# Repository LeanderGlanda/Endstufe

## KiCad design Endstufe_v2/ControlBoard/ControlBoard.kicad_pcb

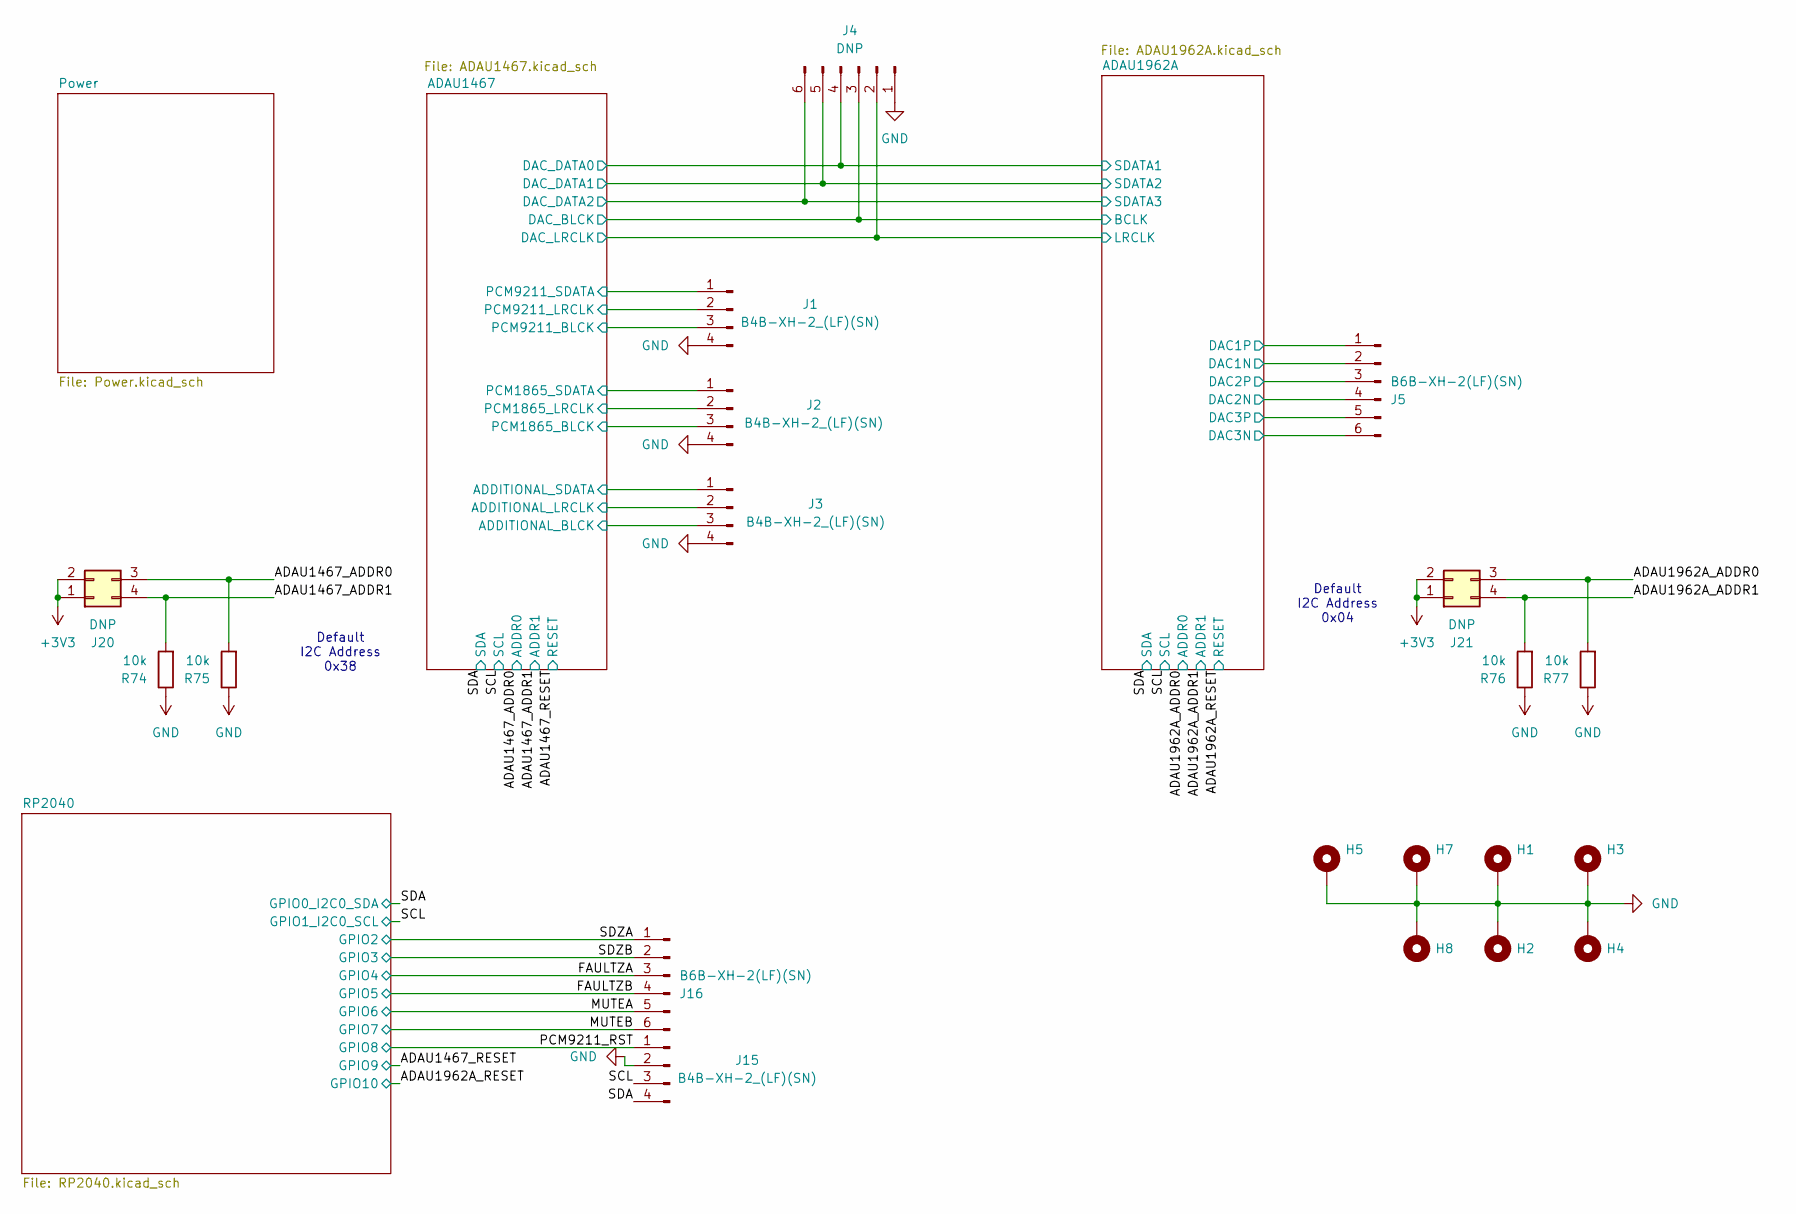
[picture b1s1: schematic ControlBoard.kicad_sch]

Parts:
H1, H2, H3, H4, H5, H7, H8: MountingHole_Pad; MountingHole_3.2mm_M3_ISO14580_Pad
J1, J2, J3, J15: B4B-XH-2_(LF)(SN); JST_XH_B4B-XH-A_1x04_P2.50mm_Vertical; LCSC C157999
J4: DNP; PinHeader_1x06_P2.54mm_Vertical
J5, J16: B6B-XH-2(LF)(SN); JST_XH_B6B-XH-A_1x06_P2.50mm_Vertical; LCSC C157986
J20, J21: DNP; PinHeader_2x02_P2.54mm_Vertical
R74, R75, R76, R77: 10k; C_0402_1005Metric; LCSC Part # C25744

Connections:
+3V3: J20.1, J20.2, J21.1, J21.2; also elsewhere on the board
/ADAU1467/ADDITIONAL_BLCK: J3.3; also elsewhere on the board
/ADAU1467/ADDITIONAL_LRCLK: J3.2; also elsewhere on the board
/ADAU1467/ADDITIONAL_SDATA: J3.1; also elsewhere on the board
/ADAU1467/DAC_BLCK: J4.3; also elsewhere on the board
/ADAU1467/DAC_DATA0: J4.4; also elsewhere on the board
/ADAU1467/DAC_DATA1: J4.5; also elsewhere on the board
/ADAU1467/DAC_DATA2: J4.6; also elsewhere on the board
/ADAU1467/DAC_LRCLK: J4.2; also elsewhere on the board
/ADAU1467/PCM1865_BLCK: J2.3; also elsewhere on the board
/ADAU1467/PCM1865_LRCLK: J2.2; also elsewhere on the board
/ADAU1467/PCM1865_SDATA: J2.1; also elsewhere on the board
/ADAU1467/PCM9211_BLCK: J1.3; also elsewhere on the board
/ADAU1467/PCM9211_LRCLK: J1.2; also elsewhere on the board
/ADAU1467/PCM9211_SDATA: J1.1; also elsewhere on the board
/ADAU1467_ADDR0: J20.3, R75.2; also elsewhere on the board
/ADAU1467_ADDR1: J20.4, R74.2; also elsewhere on the board
/ADAU1962A/DAC1N: J5.2; also elsewhere on the board
/ADAU1962A/DAC1P: J5.1; also elsewhere on the board
/ADAU1962A/DAC2N: J5.4; also elsewhere on the board
/ADAU1962A/DAC2P: J5.3; also elsewhere on the board
/ADAU1962A/DAC3N: J5.6; also elsewhere on the board
/ADAU1962A/DAC3P: J5.5; also elsewhere on the board
/ADAU1962A_ADDR0: J21.3, R77.2; also elsewhere on the board
/ADAU1962A_ADDR1: J21.4, R76.2; also elsewhere on the board
/FAULTZA: J16.3; also elsewhere on the board
/FAULTZB: J16.4; also elsewhere on the board
/MUTEA: J16.5; also elsewhere on the board
/MUTEB: J16.6; also elsewhere on the board
/PCM9211_RST: J15.1; also elsewhere on the board
/SCL: J15.3; also elsewhere on the board
/SDA: J15.4; also elsewhere on the board
/SDZA: J16.1; also elsewhere on the board
/SDZB: J16.2; also elsewhere on the board
GND: H1.1, H2.1, H3.1, H4.1, H5.1, H7.1, H8.1, J1.4, J2.4, J3.4, J4.1, J15.2, R74.1, R75.1, R76.1, R77.1; also elsewhere on the board

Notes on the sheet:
Default I2C Address 0x38
Default I2C Address 0x04

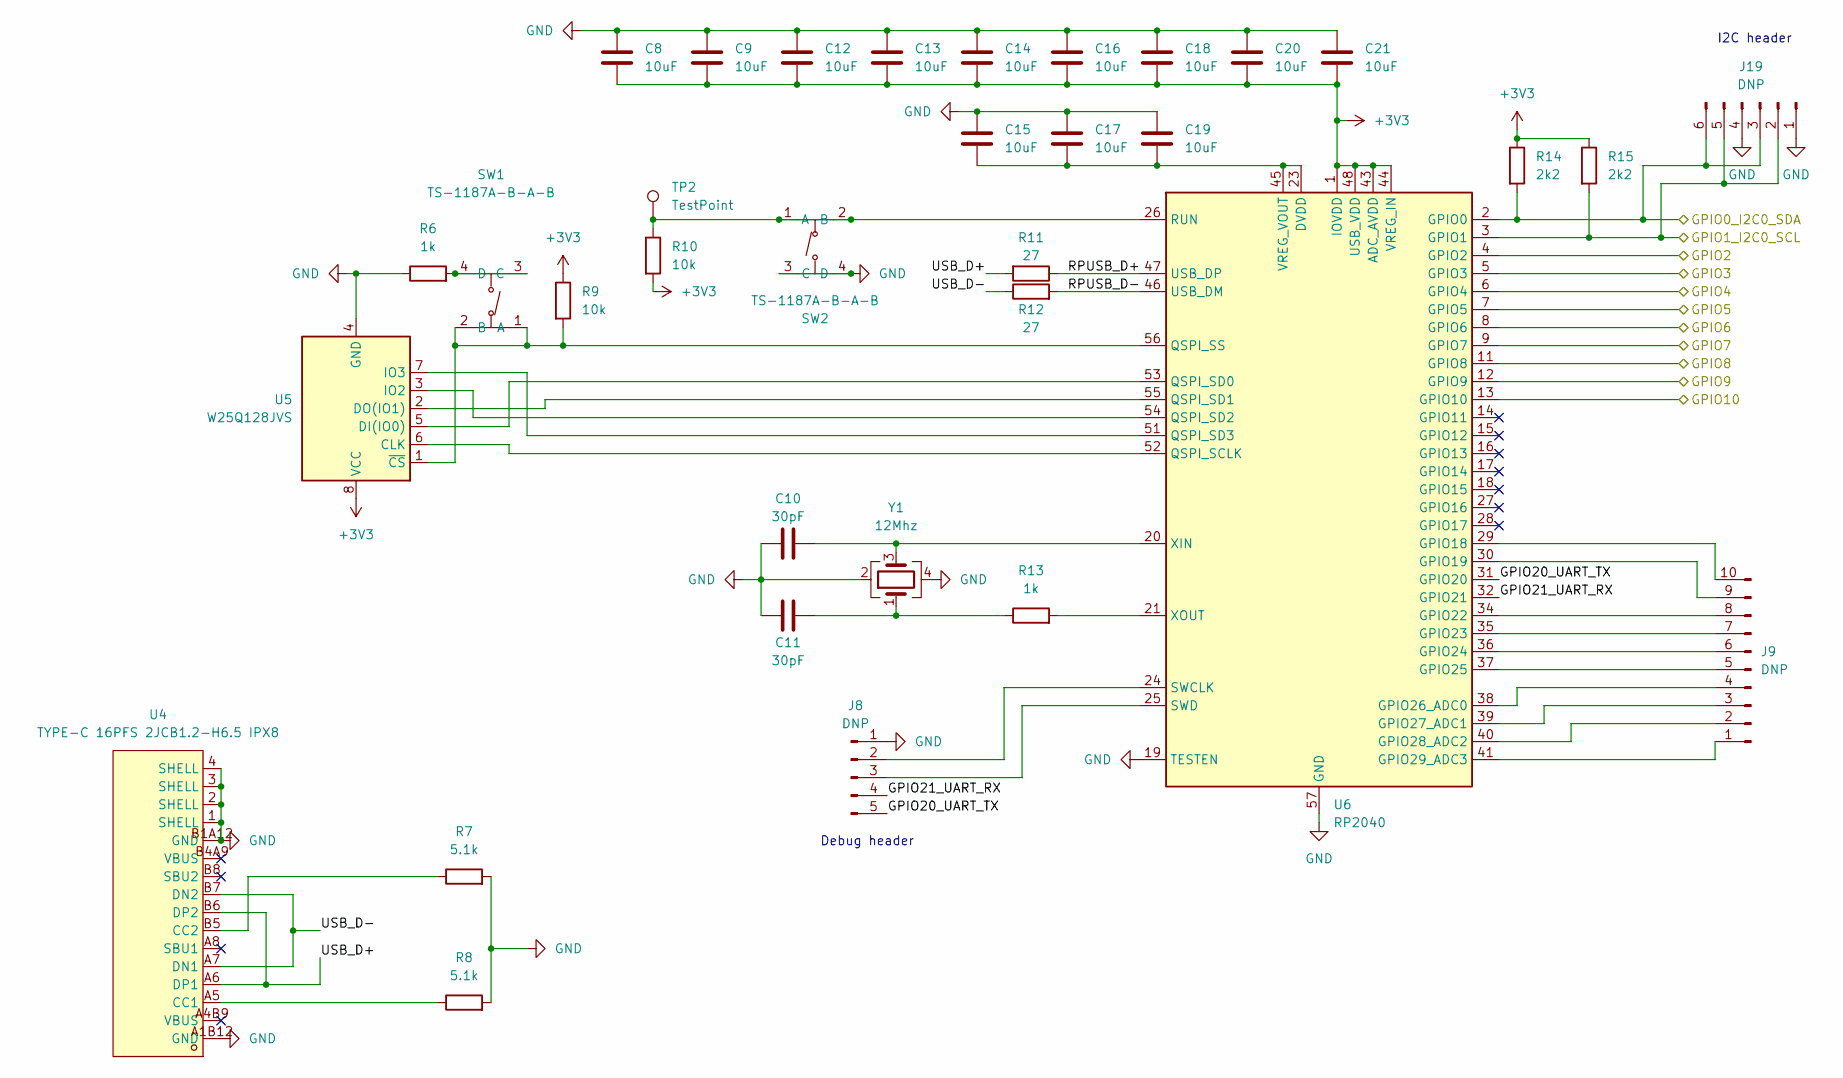
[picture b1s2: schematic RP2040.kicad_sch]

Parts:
C8, C9, C12, C13, C14, C15, C16, C17, C18, C19, C20, C21: 10uF; C_0402_1005Metric; LCSC Part # C15525
C10, C11: 30pF; C_0402_1005Metric; LCSC Part # C526980
J8: DNP; PinHeader_1x05_P2.54mm_Vertical
J9: DNP; PinHeader_1x10_P2.54mm_Vertical
J19: DNP; PinHeader_1x06_P2.54mm_Vertical
R6, R13: 1k; C_0402_1005Metric; LCSC Part # C11702
R7, R8: 5.1k; C_0603_1608Metric; LCSC Part # C2989458
R9, R10: 10k; C_0402_1005Metric; LCSC Part # C25744
R11, R12: 27; C_0603_1608Metric; LCSC Part # C2828673
R14, R15: 2k2; R_0805_2012Metric_Pad1.20x1.40mm_HandSolder; LCSC C17520
SW1, SW2: TS-1187A-B-A-B; SW-SMD_4P-L5.1-W5.1-P3.70-LS6.5-TL-2; LCSC Part # C318884
TP2: TestPoint; TestPoint_Pad_D1.0mm
U4: TYPE-C 16PFS 2JCB1.2-H6.5 IPX8; USB-C-SMD_TYPE-C16PIN; LCSC Part C393939
U5: W25Q128JVS; SOIC-8_L5.3-W5.3-P1.27-LS8.0-BL; LCSC Part # C97521
U6: RP2040; LQFN-56_L7.0-W7.0-P0.4-EP; LCSC Part # C2040
Y1: 12Mhz; OSC-SMD_4P-L3.2-W2.5-BL; LCSC Part # C9002

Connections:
+3V3: C8.2, C9.2, C12.2, C13.2, C14.2, C16.2, C18.2, C20.2, C21.2, R9.1, R10.2, R14.1, R15.1, U5.8 (VCC), U6.1 (IOVDD), U6.10 (IOVDD), U6.22 (IOVDD), U6.33 (IOVDD), U6.42 (IOVDD), U6.43 (ADC_AVDD), U6.44 (VREG_IN), U6.48 (USB_VDD), U6.49 (IOVDD); also elsewhere on the board
/ADAU1467_RESET: U6.12 (GPIO9); also elsewhere on the board
/ADAU1962A_RESET: U6.13 (GPIO10); also elsewhere on the board
/FAULTZA: U6.6 (GPIO4); also elsewhere on the board
/FAULTZB: U6.7 (GPIO5); also elsewhere on the board
/MUTEA: U6.8 (GPIO6); also elsewhere on the board
/MUTEB: U6.9 (GPIO7); also elsewhere on the board
/PCM9211_RST: U6.11 (GPIO8); also elsewhere on the board
/RP2040/GPIO20_UART_TX: J8.5, U6.31 (GPIO20)
/RP2040/GPIO21_UART_RX: J8.4, U6.32 (GPIO21)
/RP2040/RPUSB_D+: R11.1, U6.47 (USB_DP)
/RP2040/RPUSB_D-: R12.2, U6.46 (USB_DM)
/RP2040/USB_D+: R11.2, U4.A6 (DP1), U4.B6 (DP2)
/RP2040/USB_D-: R12.1, U4.A7 (DN1), U4.B7 (DN2)
/SCL: J19.2, J19.5, R15.2, U6.3 (GPIO1); also elsewhere on the board
/SDA: J19.3, J19.6, R14.2, U6.2 (GPIO0); also elsewhere on the board
/SDZA: U6.4 (GPIO2); also elsewhere on the board
/SDZB: U6.5 (GPIO3); also elsewhere on the board
GND: C8.1, C9.1, C10.1, C11.1, C12.1, C13.1, C14.1, C15.1, C16.1, C17.1, C18.1, C19.1, C20.1, C21.1, J8.1, J19.1, J19.4, R6.1, R7.2, R8.2, SW2.3 (C), SW2.4 (D), U4.1 (SHELL), U4.2 (SHELL), U4.3 (SHELL), U4.4 (SHELL), U4.A1B12 (GND), U4.B1A12 (GND), U5.4 (GND), U6.19 (TESTEN), U6.57 (GND), Y1.2, Y1.4; also elsewhere on the board
unnamed: C11.2, R13.1, Y1.1
unnamed: J8.2, U6.24 (SWCLK)
unnamed: J8.3, U6.25 (SWD)
unnamed: J9.1, U6.41 (GPIO29_ADC3)
unnamed: J9.2, U6.40 (GPIO28_ADC2)
unnamed: J9.3, U6.39 (GPIO27_ADC1)
unnamed: J9.4, U6.38 (GPIO26_ADC0)
unnamed: J9.5, U6.37 (GPIO25)
unnamed: J9.6, U6.36 (GPIO24)
unnamed: J9.7, U6.35 (GPIO23)
unnamed: J9.8, U6.34 (GPIO22)
unnamed: J9.9, U6.30 (GPIO19)
unnamed: J9.10, U6.29 (GPIO18)
unnamed: R9.2, SW1.1 (A), SW1.2 (B), U5.1 (~CS), U6.56 (QSPI_SS)
unnamed: R6.2, SW1.3 (C), SW1.4 (D)
unnamed: R10.1, SW2.1 (A), SW2.2 (B), TP2.1, U6.26 (RUN)
unnamed: R8.1, U4.A5 (CC1)
unnamed: R7.1, U4.B5 (CC2)
unnamed: U5.6 (CLK), U6.52 (QSPI_SCLK)
unnamed: U5.5 (DI(IO0)), U6.53 (QSPI_SD0)
unnamed: U5.2 (DO(IO1)), U6.55 (QSPI_SD1)
unnamed: U5.3 (IO2), U6.54 (QSPI_SD2)
unnamed: U5.7 (IO3), U6.51 (QSPI_SD3)
unnamed: C15.2, C17.2, C19.2, U6.23 (DVDD), U6.45 (VREG_VOUT), U6.50 (DVDD)
unnamed: C10.2, U6.20 (XIN), Y1.3
unnamed: R13.2, U6.21 (XOUT)

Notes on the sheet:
Debug header
I2C header

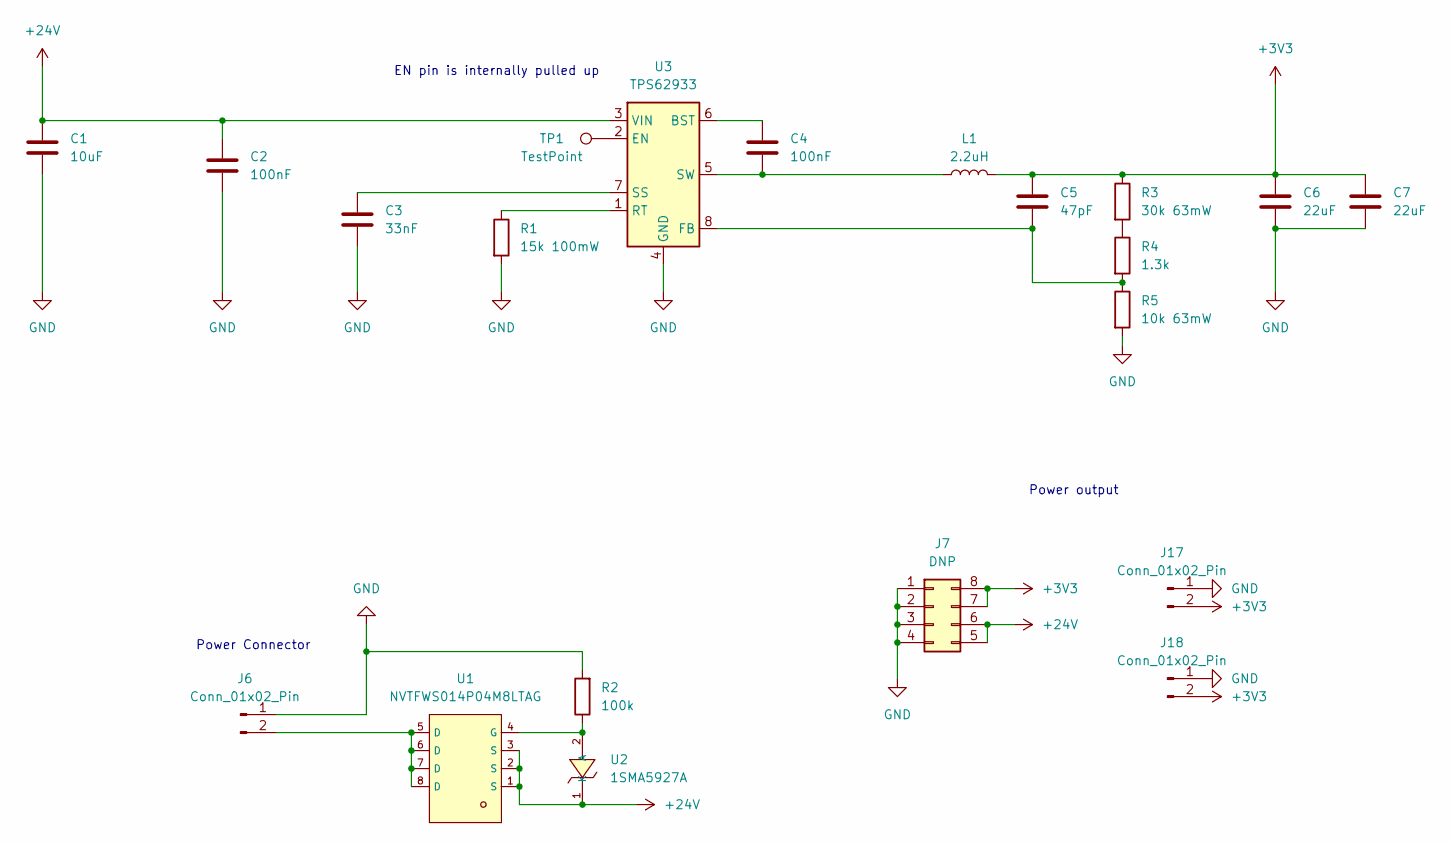
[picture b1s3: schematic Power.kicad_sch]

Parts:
C1: 10uF; C_0805_2012Metric; LCSC Part # C440198
C2, C4: 100nF; C_0402_1005Metric; LCSC Part # C307331
C3: 33nF; C_0402_1005Metric; LCSC Part # C106862
C5: 47pF; C_0402_1005Metric; LCSC Part # C1567
C6, C7: 22uF; C_0603_1608Metric; LCSC Part # C59461
J6, J17, J18: Conn_01x02_Pin; JST_XH_B2B-XH-A_1x02_P2.50mm_Vertical; LCSC Part # C158012
J7: DNP; PinHeader_2x04_P2.54mm_Vertical
L1: 2.2uH; IND-SMD_L4.4-W4.2; LCSC Part # C167206
R1: 15k 100mW; R_0402_1005Metric; LCSC Part # C413097
R2: 100k; C_0603_1608Metric; LCSC C25803
R3: 30k 63mW; R_0402_1005Metric; LCSC Part # C2961363
R4: 1.3k; R_0402_1005Metric; LCSC Part # C445599
R5: 10k 63mW; R_0402_1005Metric; LCSC Part # C25744
TP1: TestPoint; TestPoint_Pad_D1.0mm
U1: NVTFWS014P04M8LTAG; POWERPAK-1212-8_L3.1-W3.1-P0.65-LS3.3-BL-SIS402DN-T1-GE3; LCSC C900554
U2: 1SMA5927A; SMA_L4.3-W2.6-LS5.0-RD; LCSC C19077489
U3: TPS62933; SOT-583-8_L2.1-W1.2-P0.50-LS1.6-BR; LCSC Part # C6290372

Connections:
+3V3: C5.1, C6.1, C7.1, J7.7, J7.8, J17.2, J18.2, L1.2, R3.1; also elsewhere on the board
+24V: C1.1, C2.1, J7.5, J7.6, U1.1 (S), U1.2 (S), U1.3 (S), U2.1 (K), U3.3 (VIN)
GND: C1.2, C2.2, C3.2, C6.2, C7.2, J6.1, J7.1, J7.2, J7.3, J7.4, J17.1, J18.1, R1.2, R2.2, R5.2, U3.4 (GND); also elsewhere on the board
unnamed: J6.2, U1.5 (D), U1.6 (D), U1.7 (D), U1.8 (D)
unnamed: R3.2, R4.1
unnamed: R2.1, U1.4 (G), U2.2 (A)
unnamed: C4.1, U3.6 (BST)
unnamed: TP1.1, U3.2 (EN)
unnamed: C5.2, R4.2, R5.1, U3.8 (FB)
unnamed: R1.1, U3.1 (RT)
unnamed: C3.1, U3.7 (SS)
unnamed: C4.2, L1.1, U3.5 (SW)

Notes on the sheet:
Power Connector
EN pin is internally pulled up
Power output

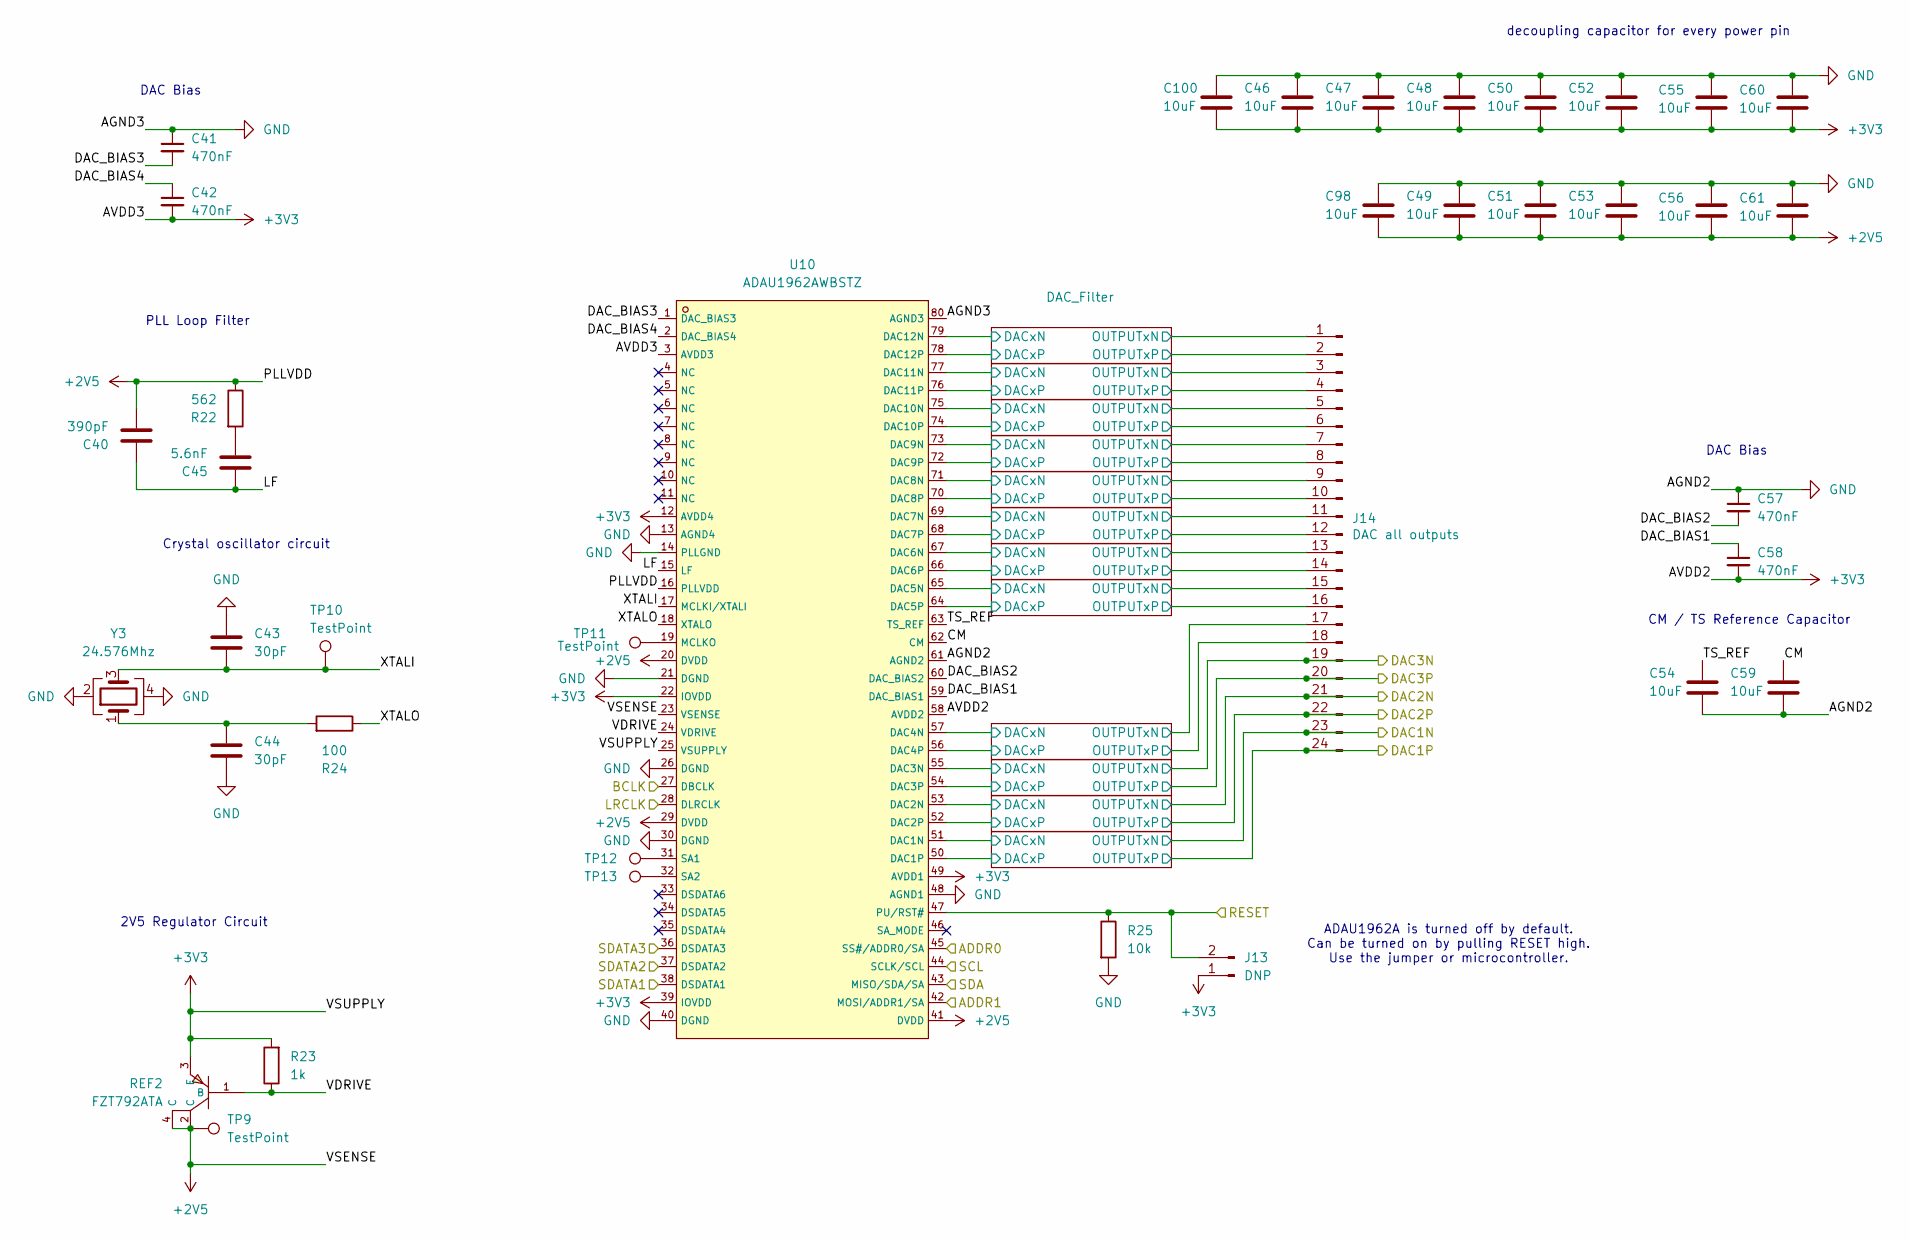
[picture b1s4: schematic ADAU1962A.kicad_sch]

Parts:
C40: 390pF; C_0603_1608Metric; LCSC C519471
C41, C42, C57, C58: 470nF; C_0402_1005Metric; LCSC C188346
C43, C44: 30pF; C_0402_1005Metric; LCSC Part # C526980
C45: 5.6nF; C_0402_1005Metric; LCSC C610180
C46, C47, C48, C49, C50, C51, C52, C53, C54, C55, C56, C59, C60, C61, C98, C100: 10uF; C_0402_1005Metric; LCSC Part # C15525
J13: DNP; PinSocket_1x02_P2.54mm_Vertical
J14: DAC all outputs; CONN-TH_24P-P2.00_B24B-PHDSS; LCSC C378937
R22: 562; R_0603_1608Metric; LCSC C3013543
R23: 1k; C_0402_1005Metric; LCSC Part # C11702
R24: 100; R_0402_1005Metric; LCSC C2902635
R25: 10k; C_0402_1005Metric; LCSC Part # C25744
REF2: FZT792ATA; SOT-223-4_L6.5-W3.5-P2.30-LS7.0-BR; LCSC C115948
TP9, TP10, TP11, TP12, TP13: TestPoint; TestPoint_Pad_D1.0mm
U10: ADAU1962AWBSTZ; LQFP-80_L14.0-W14.0-P0.65-LS16.0-BL; LCSC C654426
Y3: 24.576Mhz; OSC-SMD_4P-L3.2-W2.5-BL; LCSC Part # C2901683

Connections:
+2V5: C40.1, C49.2, C51.2, C53.2, C56.2, C61.2, C98.2, R22.1, REF2.2 (C), REF2.4 (C), TP9.1, U10.16 (PLLVDD), U10.20 (DVDD), U10.23 (VSENSE), U10.29 (DVDD), U10.41 (DVDD)
+3V3: C42.2, C46.2, C47.2, C48.2, C50.2, C52.2, C55.2, C58.2, C60.2, C100.2, J13.1, R23.2, REF2.3 (E), U10.3 (AVDD3), U10.12 (AVDD4), U10.22 (IOVDD), U10.25 (VSUPPLY), U10.39 (IOVDD), U10.49 (AVDD1), U10.58 (AVDD2); also elsewhere on the board
/ADAU1467/DAC_BLCK: U10.27 (DBCLK); also elsewhere on the board
/ADAU1467/DAC_DATA0: U10.38 (DSDATA1); also elsewhere on the board
/ADAU1467/DAC_DATA1: U10.37 (DSDATA2); also elsewhere on the board
/ADAU1467/DAC_DATA2: U10.36 (DSDATA3); also elsewhere on the board
/ADAU1467/DAC_LRCLK: U10.28 (DLRCLK); also elsewhere on the board
/ADAU1962A/CM: C59.1, U10.62 (CM)
/ADAU1962A/DAC1N: J14.23; also elsewhere on the board
/ADAU1962A/DAC1P: J14.24; also elsewhere on the board
/ADAU1962A/DAC2N: J14.21; also elsewhere on the board
/ADAU1962A/DAC2P: J14.22; also elsewhere on the board
/ADAU1962A/DAC3N: J14.19; also elsewhere on the board
/ADAU1962A/DAC3P: J14.20; also elsewhere on the board
/ADAU1962A/DAC_BIAS1: C58.1, U10.59 (DAC_BIAS1)
/ADAU1962A/DAC_BIAS2: C57.2, U10.60 (DAC_BIAS2)
/ADAU1962A/DAC_BIAS3: C41.2, U10.1 (DAC_BIAS3)
/ADAU1962A/DAC_BIAS4: C42.1, U10.2 (DAC_BIAS4)
/ADAU1962A/DAC_Filter1/DACxN: U10.77 (DAC11N); also elsewhere on the board
/ADAU1962A/DAC_Filter1/DACxP: U10.76 (DAC11P); also elsewhere on the board
/ADAU1962A/DAC_Filter1/OUTPUTxN: J14.3; also elsewhere on the board
/ADAU1962A/DAC_Filter1/OUTPUTxP: J14.4; also elsewhere on the board
/ADAU1962A/DAC_Filter2/DACxN: U10.75 (DAC10N); also elsewhere on the board
/ADAU1962A/DAC_Filter2/DACxP: U10.74 (DAC10P); also elsewhere on the board
/ADAU1962A/DAC_Filter2/OUTPUTxN: J14.5; also elsewhere on the board
/ADAU1962A/DAC_Filter2/OUTPUTxP: J14.6; also elsewhere on the board
/ADAU1962A/DAC_Filter3/DACxN: U10.73 (DAC9N); also elsewhere on the board
/ADAU1962A/DAC_Filter3/DACxP: U10.72 (DAC9P); also elsewhere on the board
/ADAU1962A/DAC_Filter3/OUTPUTxN: J14.7; also elsewhere on the board
/ADAU1962A/DAC_Filter3/OUTPUTxP: J14.8; also elsewhere on the board
/ADAU1962A/DAC_Filter4/DACxN: U10.71 (DAC8N); also elsewhere on the board
/ADAU1962A/DAC_Filter4/DACxP: U10.70 (DAC8P); also elsewhere on the board
/ADAU1962A/DAC_Filter4/OUTPUTxN: J14.9; also elsewhere on the board
/ADAU1962A/DAC_Filter4/OUTPUTxP: J14.10; also elsewhere on the board
/ADAU1962A/DAC_Filter5/DACxN: U10.69 (DAC7N); also elsewhere on the board
/ADAU1962A/DAC_Filter5/DACxP: U10.68 (DAC7P); also elsewhere on the board
/ADAU1962A/DAC_Filter5/OUTPUTxN: J14.11; also elsewhere on the board
/ADAU1962A/DAC_Filter5/OUTPUTxP: J14.12; also elsewhere on the board
/ADAU1962A/DAC_Filter6/DACxN: U10.67 (DAC6N); also elsewhere on the board
/ADAU1962A/DAC_Filter6/DACxP: U10.66 (DAC6P); also elsewhere on the board
/ADAU1962A/DAC_Filter6/OUTPUTxN: J14.13; also elsewhere on the board
/ADAU1962A/DAC_Filter6/OUTPUTxP: J14.14; also elsewhere on the board
/ADAU1962A/DAC_Filter7/DACxN: U10.65 (DAC5N); also elsewhere on the board
/ADAU1962A/DAC_Filter7/DACxP: U10.64 (DAC5P); also elsewhere on the board
/ADAU1962A/DAC_Filter7/OUTPUTxN: J14.15; also elsewhere on the board
/ADAU1962A/DAC_Filter7/OUTPUTxP: J14.16; also elsewhere on the board
/ADAU1962A/DAC_Filter8/DACxN: U10.57 (DAC4N); also elsewhere on the board
/ADAU1962A/DAC_Filter8/DACxP: U10.56 (DAC4P); also elsewhere on the board
/ADAU1962A/DAC_Filter8/OUTPUTxN: J14.17; also elsewhere on the board
/ADAU1962A/DAC_Filter8/OUTPUTxP: J14.18; also elsewhere on the board
/ADAU1962A/DAC_Filter9/DACxN: U10.55 (DAC3N); also elsewhere on the board
/ADAU1962A/DAC_Filter9/DACxP: U10.54 (DAC3P); also elsewhere on the board
/ADAU1962A/DAC_Filter10/DACxN: U10.53 (DAC2N); also elsewhere on the board
/ADAU1962A/DAC_Filter10/DACxP: U10.52 (DAC2P); also elsewhere on the board
/ADAU1962A/DAC_Filter11/DACxN: U10.51 (DAC1N); also elsewhere on the board
/ADAU1962A/DAC_Filter11/DACxP: U10.50 (DAC1P); also elsewhere on the board
/ADAU1962A/DAC_Filter/DACxN: U10.79 (DAC12N); also elsewhere on the board
/ADAU1962A/DAC_Filter/DACxP: U10.78 (DAC12P); also elsewhere on the board
/ADAU1962A/DAC_Filter/OUTPUTxN: J14.1; also elsewhere on the board
/ADAU1962A/DAC_Filter/OUTPUTxP: J14.2; also elsewhere on the board
/ADAU1962A/LF: C40.2, C45.2, U10.15 (LF)
/ADAU1962A/TS_REF: C54.1, U10.63 (TS_REF)
/ADAU1962A/VDRIVE: R23.1, REF2.1 (B), U10.24 (VDRIVE)
/ADAU1962A/XTALI: C43.2, TP10.1, U10.17 (MCLKI/XTALI), Y3.3
/ADAU1962A/XTALO: R24.1, U10.18 (XTALO)
/ADAU1962A_ADDR0: U10.45 (SS#/ADDR0/SA); also elsewhere on the board
/ADAU1962A_ADDR1: U10.42 (MOSI/ADDR1/SA); also elsewhere on the board
/ADAU1962A_RESET: J13.2, R25.1, U10.47 (PU/RST#); also elsewhere on the board
/SCL: U10.44 (SCLK/SCL); also elsewhere on the board
/SDA: U10.43 (MISO/SDA/SA); also elsewhere on the board
GND: C41.1, C43.1, C44.2, C46.1, C47.1, C48.1, C49.1, C50.1, C51.1, C52.1, C53.1, C54.2, C55.1, C56.1, C57.1, C59.2, C60.1, C61.1, C98.1, C100.1, R25.2, U10.13 (AGND4), U10.14 (PLLGND), U10.21 (DGND), U10.26 (DGND), U10.30 (DGND), U10.40 (DGND), U10.48 (AGND1), U10.61 (AGND2), U10.80 (AGND3), Y3.2, Y3.4; also elsewhere on the board
unnamed: C44.1, R24.2, Y3.1
unnamed: C45.1, R22.2
unnamed: TP11.1, U10.19 (MCLKO)
unnamed: TP12.1, U10.31 (SA1)
unnamed: TP13.1, U10.32 (SA2)

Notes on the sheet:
Crystal oscillator circuit
PLL Loop Filter
DAC Bias
ADAU1962A is turned off by default. Can be turned on by pulling RESET high. Use the jumper or microcontroller.
CM / TS Reference Capacitor
decoupling capacitor for every power pin
2V5 Regulator Circuit

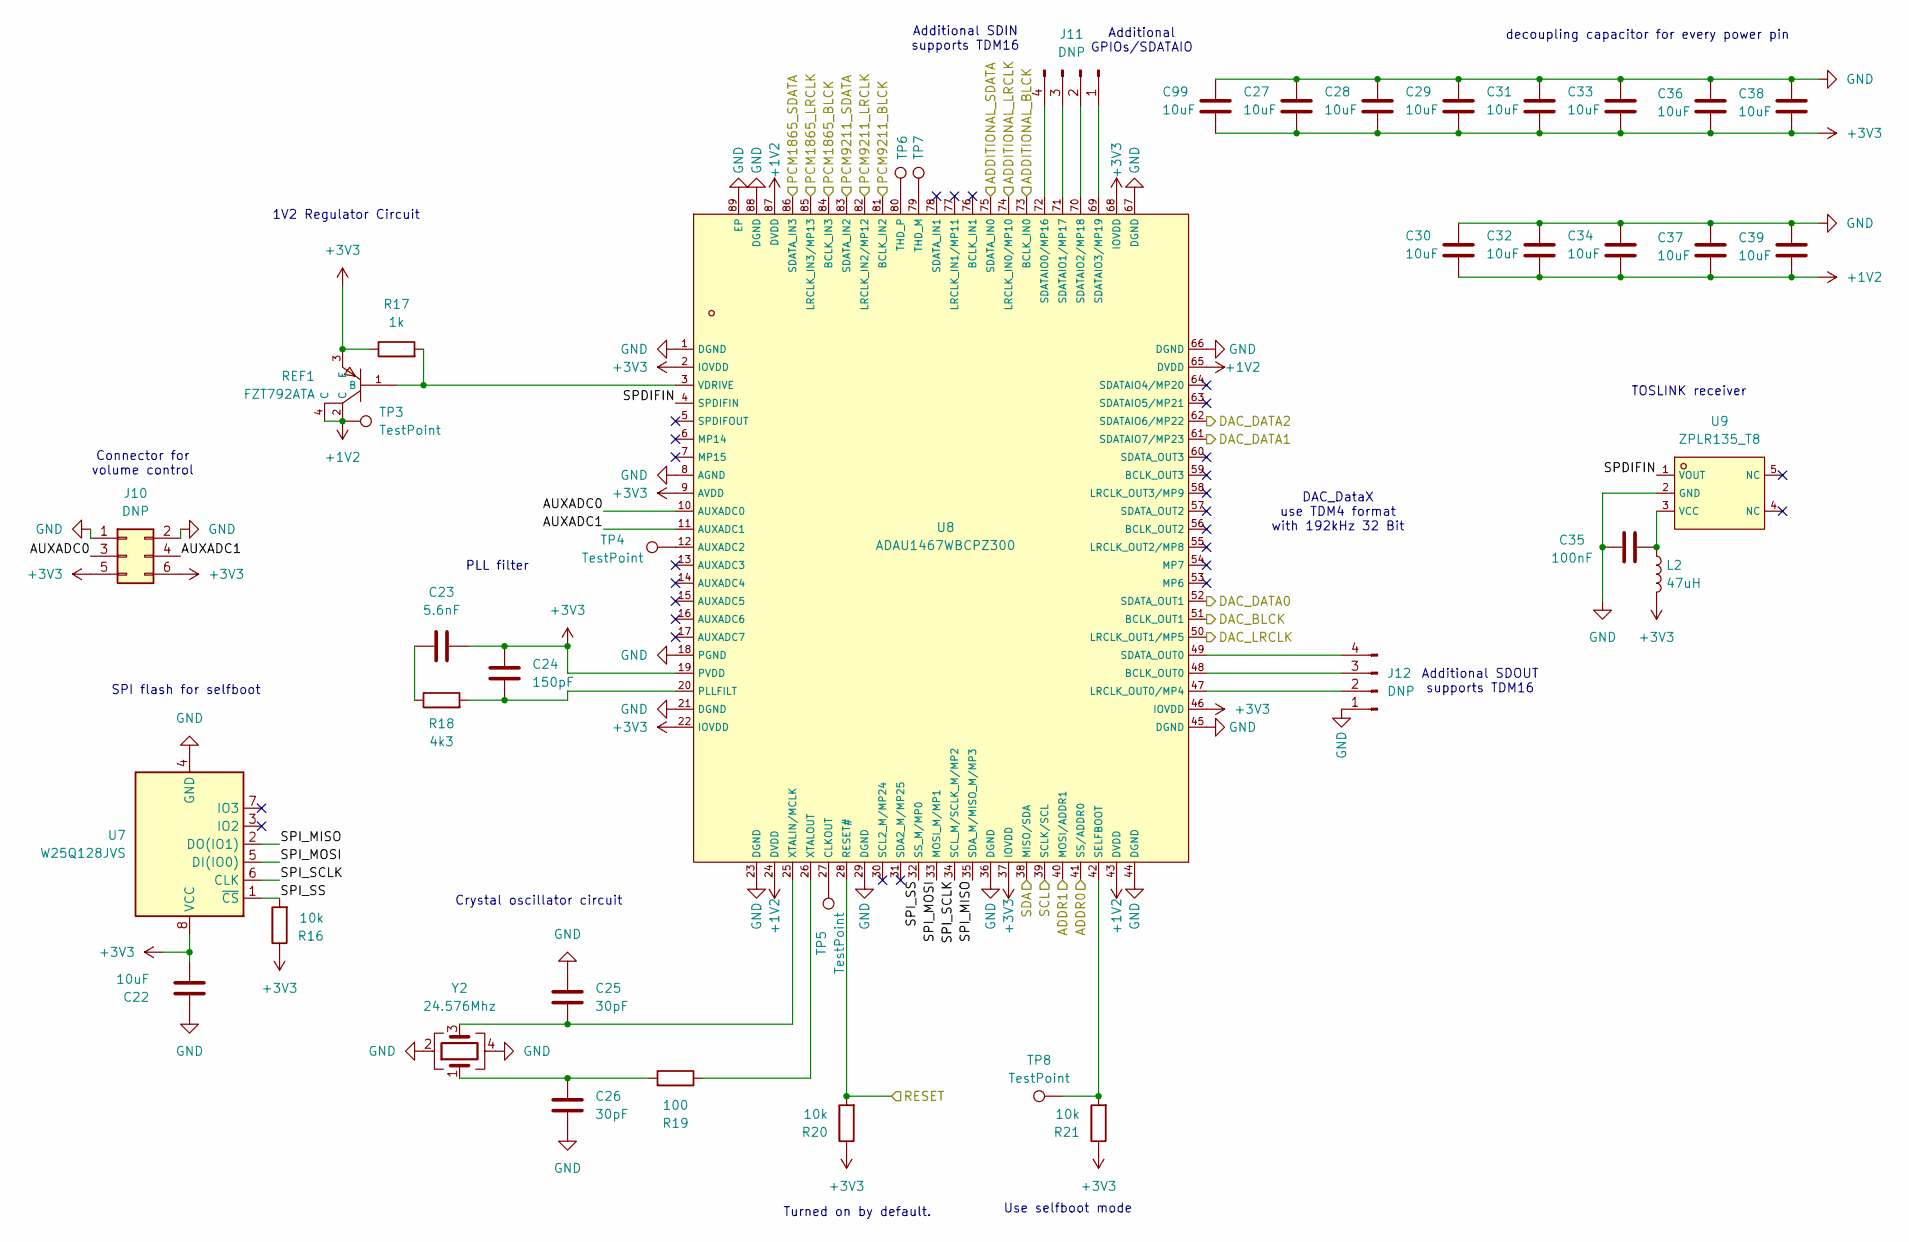
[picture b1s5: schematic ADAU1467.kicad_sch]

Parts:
C22, C27, C28, C29, C30, C31, C32, C33, C34, C36, C37, C38, C39, C99: 10uF; C_0402_1005Metric; LCSC Part # C15525
C23: 5.6nF; C_0402_1005Metric; LCSC C610180
C24: 150pF; C_0402_1005Metric; LCSC C412459
C25, C26: 30pF; C_0402_1005Metric; LCSC Part # C526980
C35: 100nF; C_0402_1005Metric; LCSC Part # C307331
J10: DNP; PinHeader_2x03_P2.54mm_Vertical
J11: DNP; PinHeader_1x04_P2.54mm_Vertical
J12: DNP; JST_XH_B4B-XH-A_1x04_P2.50mm_Vertical; JLCPCB Position Offset 0,-0.5
L2: 47uH; L_0805_2012Metric; LCSC C383408
R16, R20, R21: 10k; C_0402_1005Metric; LCSC Part # C25744
R17: 1k; C_0402_1005Metric; LCSC Part # C11702
R18: 4k3; R_0603_1608Metric; LCSC C2692818
R19: 100; R_0402_1005Metric; LCSC C2902635
REF1: FZT792ATA; SOT-223-4_L6.5-W3.5-P2.30-LS7.0-BR; LCSC C115948
TP3, TP4, TP5, TP6, TP7, TP8: TestPoint; TestPoint_Pad_D1.0mm
U7: W25Q128JVS; SOIC-8_L5.3-W5.3-P1.27-LS8.0-BL; LCSC Part # C97521
U8: ADAU1467WBCPZ300; LFCSP-88_L12.0-W12.0-P0.50-BL-EP5.3; LCSC C654415
U9: ZPLR135_T8; CONN-TH_ZPLR135-T8; LCSC C277778
Y2: 24.576Mhz; OSC-SMD_4P-L3.2-W2.5-BL; LCSC Part # C2901683

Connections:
+1V2: C30.2, C32.2, C34.2, C37.2, C39.2, REF1.2 (C), REF1.4 (C), TP3.1, U8.24 (DVDD), U8.43 (DVDD), U8.65 (DVDD), U8.87 (DVDD)
+3V3: C22.2, C23.2, C24.1, C27.2, C28.2, C29.2, C31.2, C33.2, C36.2, C38.2, C99.2, J10.5, J10.6, L2.2, R16.1, R17.1, R20.1, R21.1, REF1.3 (E), U7.8 (VCC), U8.2 (IOVDD), U8.9 (AVDD), U8.19 (PVDD), U8.22 (IOVDD), U8.37 (IOVDD), U8.46 (IOVDD), U8.68 (IOVDD); also elsewhere on the board
/ADAU1467/ADDITIONAL_BLCK: U8.73 (BCLK_IN0); also elsewhere on the board
/ADAU1467/ADDITIONAL_LRCLK: U8.74 (LRCLK_IN0/MP10); also elsewhere on the board
/ADAU1467/ADDITIONAL_SDATA: U8.75 (SDATA_IN0); also elsewhere on the board
/ADAU1467/AUXADC0: J10.3, U8.10 (AUXADC0)
/ADAU1467/AUXADC1: J10.4, U8.11 (AUXADC1)
/ADAU1467/DAC_BLCK: U8.51 (BCLK_OUT1); also elsewhere on the board
/ADAU1467/DAC_DATA0: U8.52 (SDATA_OUT1); also elsewhere on the board
/ADAU1467/DAC_DATA1: U8.61 (SDATAIO7/MP23); also elsewhere on the board
/ADAU1467/DAC_DATA2: U8.62 (SDATAIO6/MP22); also elsewhere on the board
/ADAU1467/DAC_LRCLK: U8.50 (LRCLK_OUT1/MP5); also elsewhere on the board
/ADAU1467/PCM1865_BLCK: U8.84 (BCLK_IN3); also elsewhere on the board
/ADAU1467/PCM1865_LRCLK: U8.85 (LRCLK_IN3/MP13); also elsewhere on the board
/ADAU1467/PCM1865_SDATA: U8.86 (SDATA_IN3); also elsewhere on the board
/ADAU1467/PCM9211_BLCK: U8.81 (BCLK_IN2); also elsewhere on the board
/ADAU1467/PCM9211_LRCLK: U8.82 (LRCLK_IN2/MP12); also elsewhere on the board
/ADAU1467/PCM9211_SDATA: U8.83 (SDATA_IN2); also elsewhere on the board
/ADAU1467/SPDIFIN: U8.4 (SPDIFIN), U9.1 (VOUT)
/ADAU1467/SPI_MISO: U7.2 (DO(IO1)), U8.35 (SDA_M/MISO_M/MP3)
/ADAU1467/SPI_MOSI: U7.5 (DI(IO0)), U8.33 (MOSI_M/MP1)
/ADAU1467/SPI_SCLK: U7.6 (CLK), U8.34 (SCL_M/SCLK_M/MP2)
/ADAU1467/SPI_SS: R16.2, U7.1 (~CS), U8.32 (SS_M/MP0)
/ADAU1467_ADDR0: U8.41 (SS/ADDR0); also elsewhere on the board
/ADAU1467_ADDR1: U8.40 (MOSI/ADDR1); also elsewhere on the board
/ADAU1467_RESET: R20.2, U8.28 (RESET#); also elsewhere on the board
/SCL: U8.39 (SCLK/SCL); also elsewhere on the board
/SDA: U8.38 (MISO/SDA); also elsewhere on the board
GND: C22.1, C25.1, C26.2, C27.1, C28.1, C29.1, C30.1, C31.1, C32.1, C33.1, C34.1, C35.1, C36.1, C37.1, C38.1, C39.1, C99.1, J10.1, J10.2, J12.1, U7.4 (GND), U8.1 (DGND), U8.8 (AGND), U8.18 (PGND), U8.21 (DGND), U8.23 (DGND), U8.29 (DGND), U8.36 (DGND), U8.44 (DGND), U8.45 (DGND), U8.66 (DGND), U8.67 (DGND), U8.88 (DGND), U8.89 (EP), U9.2 (GND), Y2.2, Y2.4; also elsewhere on the board
unnamed: C23.1, R18.1
unnamed: C26.1, R19.2, Y2.1
unnamed: J11.1, U8.69 (SDATAIO3/MP19)
unnamed: J11.2, U8.70 (SDATAIO2/MP18)
unnamed: J11.3, U8.71 (SDATAIO1/MP17)
unnamed: J11.4, U8.72 (SDATAIO0/MP16)
unnamed: J12.2, U8.47 (LRCLK_OUT0/MP4)
unnamed: J12.3, U8.48 (BCLK_OUT0)
unnamed: J12.4, U8.49 (SDATA_OUT0)
unnamed: R17.2, REF1.1 (B), U8.3 (VDRIVE)
unnamed: TP4.1, U8.12 (AUXADC2)
unnamed: TP5.1, U8.27 (CLKOUT)
unnamed: C24.2, R18.2, U8.20 (PLLFILT)
unnamed: R21.2, TP8.1, U8.42 (SELFBOOT)
unnamed: TP7.1, U8.79 (THD_M)
unnamed: TP6.1, U8.80 (THD_P)
unnamed: C25.2, U8.25 (XTALIN/MCLK), Y2.3
unnamed: R19.1, U8.26 (XTALOUT)
unnamed: C35.2, L2.1, U9.3 (VCC)

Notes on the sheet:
Crystal oscillator circuit
DAC_DataX use TDM4 format with 192kHz 32 Bit
decoupling capacitor for every power pin
Connector for volume control
SPI flash for selfboot
Turned on by default.
Additional SDOUT supports TDM16
Additional GPIOs/SDATAIO
1V2 Regulator Circuit
PLL filter
Additional SDIN supports TDM16
TOSLINK receiver
Use selfboot mode
